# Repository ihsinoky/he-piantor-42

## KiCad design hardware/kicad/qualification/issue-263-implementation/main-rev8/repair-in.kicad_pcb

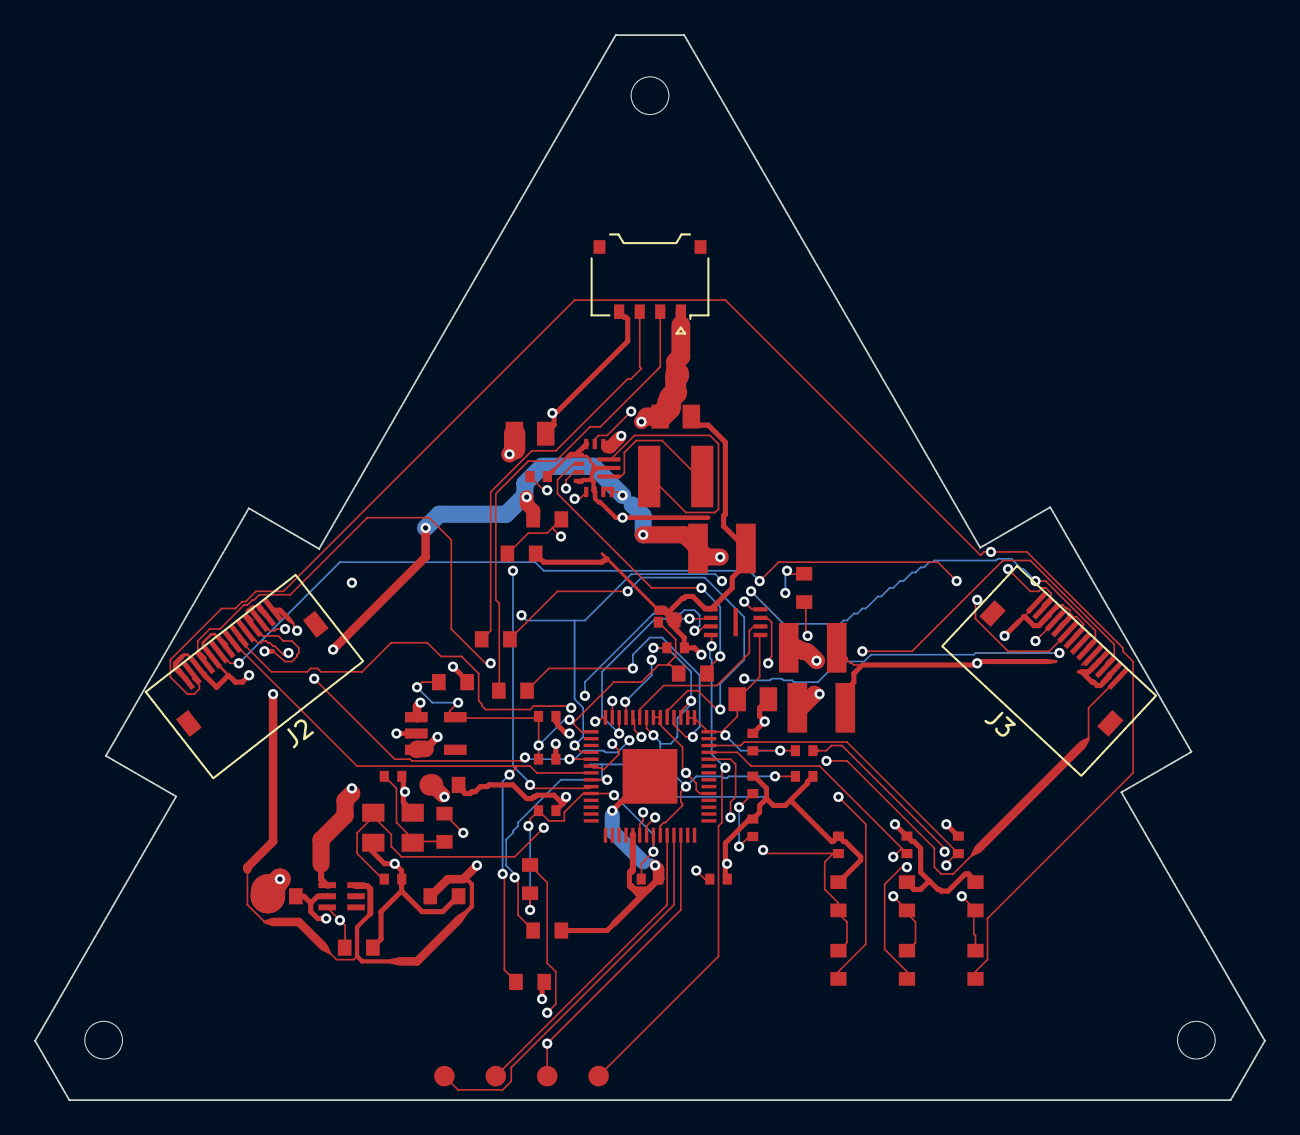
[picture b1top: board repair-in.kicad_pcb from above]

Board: 4 copper layers, 71.8 x 62.2 mm, 62 parts (0 on the bottom side), 40 nets.

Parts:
C1: 15pF; C1
C2: 15pF; C2
C3: 100nF; C3
C4: 100nF; C4
C5: 100nF; C5
C6: 100nF; C6
C7: 100nF; C7
C8: 100nF; C8
C9: 100nF; C9
C10: 100nF; C10
C11: 100nF; C11
C12: 1uF; C12
C13: 1uF; C13
C14: 10uF; C14
C15: 100nF; C15
C16: 1uF; C16
C17: 1uF; C17
C18: 1uF; C18
C19: 1uF; C19
C20: 1nF; C20
C21: 1nF; C21
C22: 1nF; C22
C23: 22uF 16V X6S 0805; C23
C24: 22uF 16V X6S 0805; C24
C25: 100nF; C25
C26: 22uF 16V X7R 1210; C26
C27: 22uF 16V X7R 1210; C27
C28: 22uF 16V X7R 1210; C28
H1: NPTH_2.2mm; H1
H2: NPTH_2.2mm; H2
H3: NPTH_2.2mm; H3
J2, J3: FH12-14S-0.5SH(55); Hirose_FH12-14S-0.5SH_1x14-1MP_P0.50mm_Horizontal
J4: 781710004; J4
L1: 1.5uH XFL4020-152MEC; L1
R3: 27; R3
R4: 27; R4
R5: 1k; R5
R6: 100k; R6
R7: 100k; R7
R8: 10k; R8
R9: 1k; R9
R10: 6.8k; R10
R11: 10k; R11
R12: 6.8k; R12
R13: 10k; R13
R14: 6.8k; R14
R15: 10k; R15
R16: 100k; R16
R17: 54.9k 0.1% 25ppm/K; R17
R18: 10k 0.1% 25ppm/K; R18
R19: 100k; R19
TP1: TestPoint; TP1
TP2: TestPoint; TP2
TP3: TestPoint; TP3
TP4: TestPoint; TP4
U1: RP2040; U1
U3: W25Q16JVUXIQ; U3
U4: AP2112K-3.3TRG1; U4
U5: TPS22919DCKR; U5
U6: TPS63070RNMR; U6
Y1: ABM8-272-T3; Y1

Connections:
ADC_A: C20.1, R10.2, R11.1, U1.38
ADC_B: C21.1, R12.2, R13.1, U1.39
ADC_C: C22.1, R14.2, R15.1, U1.40
FB_5V2: R17.2, R18.1, U6.5
GND: C1.2, C2.2, C3.2, C4.2, C5.2, C6.2, C7.2, C8.2, C9.2, C10.2, C11.2, C12.2, C13.2, C14.2, C15.2, C16.2, C17.2, C18.2, C19.2, C20.2, C21.2, C22.2, C23.2, C24.2, C25.2, C26.2, C27.2, C28.2, J2.1, J2.3, J2.5, J2.7, J2.11, J2.13, J3.1, J3.3, J3.5, J3.7, J3.11, J3.13, J4.4, R6.2, R7.2, R11.2, R13.2, R15.2, R16.2, R18.2, U1.19, U1.57, U3.4, U4.2, U5.2, U6.1, U6.4, U6.6, U6.10, U6.15, Y1.2, Y1.4
HALL_5V: C19.1, J2.14, J3.14, U5.6
HALL_PWR_EN: R7.1, U1.9, U5.3, U6.14
MUX_A0: J2.12, J3.12, U1.4
MUX_A1: J2.10, J3.10, U1.5
MUX_A2: J2.9, J3.9, U1.6
MUX_EN1: J3.8, R16.1, U1.8
MUX_OUT_A: J2.6, J3.6, R10.1
MUX_OUT_B: J2.4, J3.4, R12.1
MUX_OUT_C: J2.2, J3.2, R14.1
QSPI_SCLK: U1.52, U3.6
QSPI_SD0: U1.53, U3.5
QSPI_SD1: U1.55, U3.2
QSPI_SD2: U1.54, U3.3
QSPI_SD3: U1.51, U3.7
QSPI_SS_FLASH: R5.2, TP4.1, U3.1
QSPI_SS_MCU: R5.1, U1.56
RAIL_PG: R19.2, U6.2
RUN: R8.2, TP3.1, U1.26
SW1: L1.1, U6.11
SW2: L1.2, U6.9
SWCLK: TP2.1, U1.24
SWDIO: TP1.1, U1.25
USB_DM: R4.2, U1.46
USB_DM_ESD: J4.2, R4.1
USB_DP: R3.2, U1.47
USB_DP_ESD: J4.3, R3.1
V1V1: C11.1, C13.1, U1.23, U1.45, U1.50
V3V3: C3.1, C4.1, C5.1, C6.1, C7.1, C8.1, C9.1, C10.1, C12.1, C14.1, C15.1, C17.1, R8.1, R19.1, U1.1, U1.10, U1.22, U1.33, U1.42, U1.43, U1.44, U1.48, U1.49, U3.8, U4.5
V5V2: C26.1, C27.1, C28.1, R17.1, U5.1, U6.7, U6.8
VAUX: C25.1, U6.3
VBUS: C16.1, C18.1, C23.1, C24.1, J4.1, U4.1, U4.3, U6.12, U6.13
WING_EN: J2.8, R6.1, U1.7
XIN: C1.1, U1.20, Y1.1
XOUT: R9.2, U1.21
XOUT_XTAL: C2.1, R9.1, Y1.3

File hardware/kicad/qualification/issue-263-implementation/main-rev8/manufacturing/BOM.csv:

Comment,Designator,Footprint,LCSC Part #,Quantity
1.5uH XFL4020-152MEC,L1,L1,,1
100k,R16,R16,,1
100k,R19,R19,,1
100k,R6,R6,,1
100k,R7,R7,,1
100nF,C10,C10,,1
100nF,C11,C11,,1
100nF,C15,C15,,1
100nF,C25,C25,,1
100nF,C3,C3,,1
100nF,C4,C4,,1
100nF,C5,C5,,1
100nF,C6,C6,,1
100nF,C7,C7,,1
100nF,C8,C8,,1
100nF,C9,C9,,1
10k,R11,R11,,1
10k,R13,R13,,1
10k,R15,R15,,1
10k,R8,R8,,1
10k 0.1% 25ppm/K,R18,R18,,1
10uF,C14,C14,,1
15pF,C1,C1,,1
15pF,C2,C2,,1
1k,R5,R5,,1
1k,R9,R9,,1
1nF,C20,C20,,1
1nF,C21,C21,,1
1nF,C22,C22,,1
1uF,C12,C12,,1
1uF,C13,C13,,1
1uF,C16,C16,,1
1uF,C17,C17,,1
1uF,C18,C18,,1
1uF,C19,C19,,1
22uF 16V X6S 0805,C23,C23,,1
22uF 16V X6S 0805,C24,C24,,1
22uF 16V X7R 1210,C26,C26,,1
22uF 16V X7R 1210,C27,C27,,1
22uF 16V X7R 1210,C28,C28,,1
27,R3,R3,,1
27,R4,R4,,1
54.9k 0.1% 25ppm/K,R17,R17,,1
6.8k,R10,R10,,1
6.8k,R12,R12,,1
6.8k,R14,R14,,1
781710004,J4,J4,,1
ABM8-272-T3,Y1,Y1,,1
AP2112K-3.3TRG1,U4,U4,,1
FH12-14S-0.5SH(55),"J2,J3",Hirose_FH12-14S-0.5SH_1x14-1MP_P0.50mm_Horizontal,C-HIROSE-FH12-14S,2
NPTH_2.2mm,H1,H1,,1
NPTH_2.2mm,H2,H2,,1
NPTH_2.2mm,H3,H3,,1
RP2040,U1,U1,,1
TPS22919DCKR,U5,U5,,1
TPS63070RNMR,U6,U6,,1
TestPoint,TP1,TP1,,1
TestPoint,TP2,TP2,,1
TestPoint,TP3,TP3,,1
TestPoint,TP4,TP4,,1
W25Q16JVUXIQ,U3,U3,,1

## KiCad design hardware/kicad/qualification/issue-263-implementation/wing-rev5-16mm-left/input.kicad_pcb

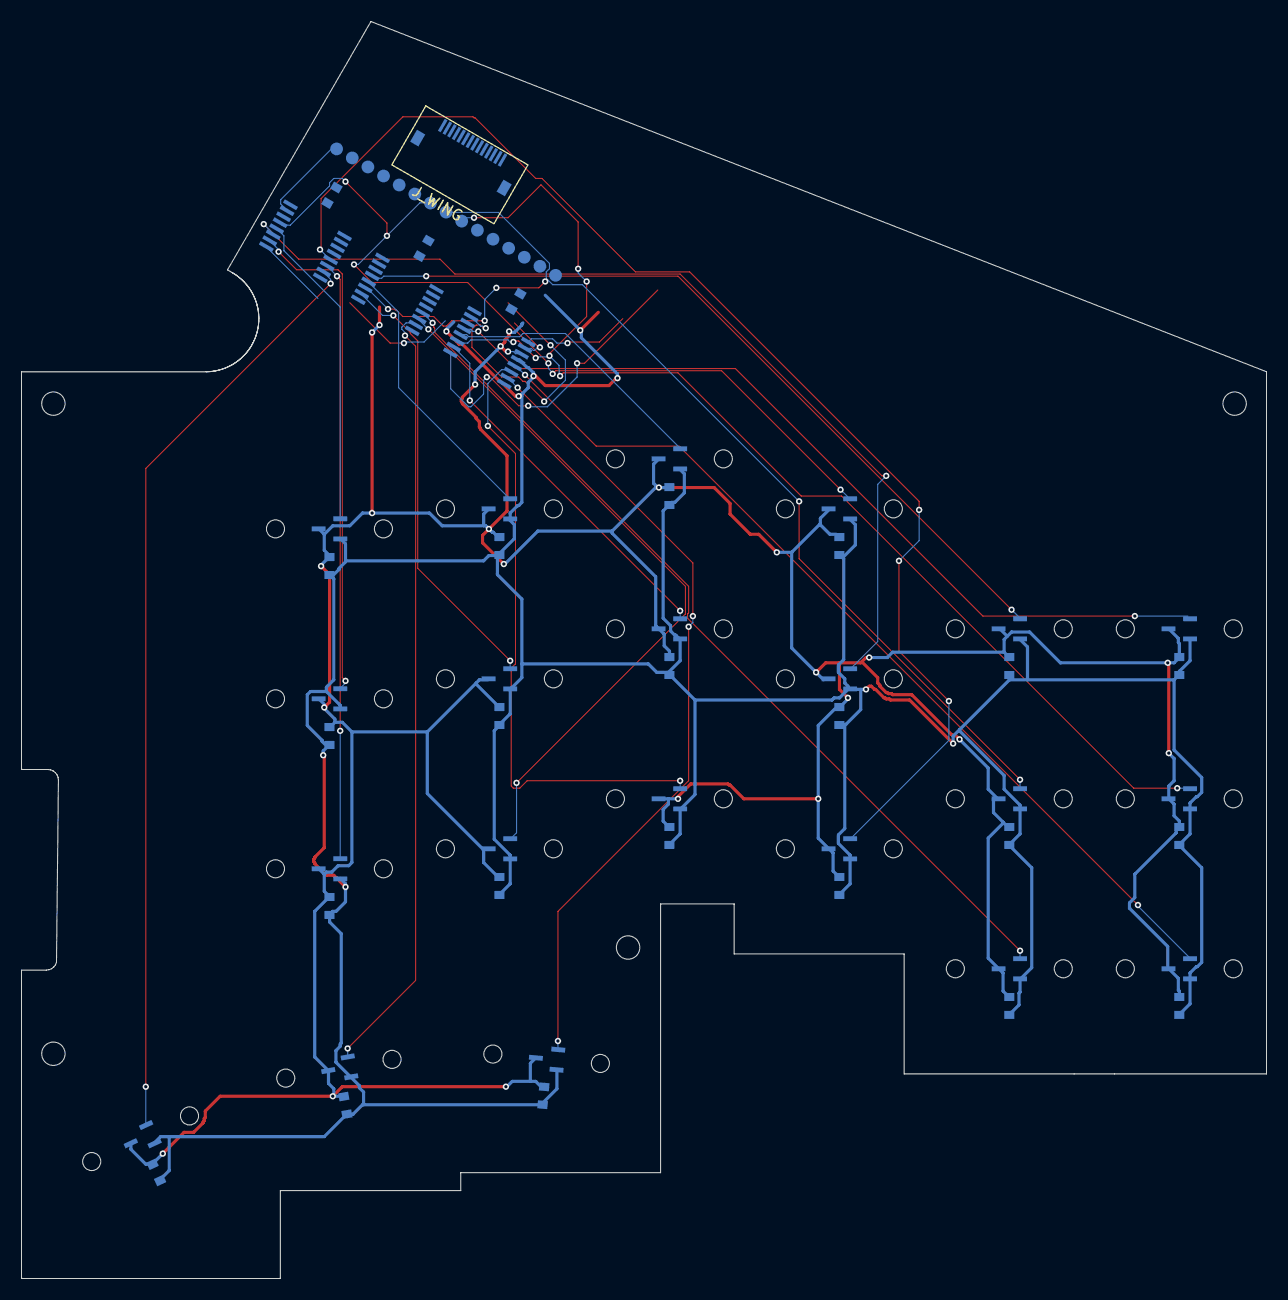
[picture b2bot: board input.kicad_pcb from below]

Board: 2 copper layers, 117.2 x 118.3 mm, 110 parts (64 on the bottom side), 30 nets.

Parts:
C_HA0, C_HA1, C_HA2, C_HA3, C_HA4, C_HA5, C_HA6: GRM188R71C104KA01D; capacitor
C_HB0, C_HB1, C_HB2, C_HB3, C_HB4, C_HB5, C_HB6: GRM188R71C104KA01D; capacitor
C_HC0, C_HC1, C_HC2, C_HC3, C_HC4, C_HC5, C_HC6: GRM188R71C104KA01D; capacitor
C_MUX_A: GRM188R71C104KA01D; capacitor
C_MUX_B: GRM188R71C104KA01D; capacitor
C_MUX_C: GRM188R71C104KA01D; capacitor
H1, H2, H3, H4: NPTH_2.2; NPTH
J_WING: FH12-14S-0.5SH(55); Hirose_FH12-14S-0.5SH_1x14-1MP_P0.50mm_Horizontal
MH_1_1, MH_1_2, MH_2_1, MH_2_2, MH_3_1, MH_3_2, MH_4_1, MH_4_2, MH_5_1, MH_5_2, MH_6_1, MH_6_2, MH_7_1, MH_7_2, MH_8_1, MH_8_2, MH_9_1, MH_9_2, MH_10_1, MH_10_2, MH_11_1, MH_11_2, MH_12_1, MH_12_2, MH_13_1, MH_13_2, MH_14_1, MH_14_2, MH_15_1, MH_15_2, MH_16_1, MH_16_2, MH_17_1, MH_17_2, MH_18_1, MH_18_2, MH_19_1, MH_19_2, MH_20_1, MH_20_2, MH_21_1, MH_21_2: NPTH_1.7; NPTH
TP_H_CTR_RAW: PCB_PAD_1.2MM; testpoint
TP_H_DIAG_RAW: PCB_PAD_1.2MM; testpoint
TP_H_N_RAW: PCB_PAD_1.2MM; testpoint
TP_W_A0, TP_W_A1, TP_W_A2: PCB_PAD_1.2MM; testpoint
TP_W_EN: PCB_PAD_1.2MM; testpoint
TP_W_GND: PCB_PAD_1.2MM; testpoint
TP_W_GND_A: PCB_PAD_1.2MM; testpoint
TP_W_GND_B: PCB_PAD_1.2MM; testpoint
TP_W_GND_C: PCB_PAD_1.2MM; testpoint
TP_W_H5V: PCB_PAD_1.2MM; testpoint
TP_W_MUXA: PCB_PAD_1.2MM; testpoint
TP_W_MUXB: PCB_PAD_1.2MM; testpoint
TP_W_MUXC: PCB_PAD_1.2MM; testpoint
U_HA0, U_HA1, U_HA2, U_HA3, U_HA4, U_HA5, U_HA6: DRV5055A3QDBZR; hall
U_HB0, U_HB1, U_HB2, U_HB3, U_HB4, U_HB5, U_HB6: DRV5055A3QDBZR; hall
U_HC0, U_HC1, U_HC2, U_HC3, U_HC4, U_HC5, U_HC6: DRV5055A3QDBZR; hall
U_MUX_A: TMUX1208PWR; mux
U_MUX_B: TMUX1208PWR; mux
U_MUX_C: TMUX1208PWR; mux

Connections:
GND: C_HA0.2, C_HA1.2, C_HA2.2, C_HA3.2, C_HA4.2, C_HA5.2, C_HA6.2, C_HB0.2, C_HB1.2, C_HB2.2, C_HB3.2, C_HB4.2, C_HB5.2, C_HB6.2, C_HC0.2, C_HC1.2, C_HC2.2, C_HC3.2, C_HC4.2, C_HC5.2, C_HC6.2, C_MUX_A.2, C_MUX_B.2, C_MUX_C.2, J_WING.2, J_WING.4, J_WING.8, J_WING.10, J_WING.12, J_WING.14, TP_W_GND.1, TP_W_GND_A.1, TP_W_GND_B.1, TP_W_GND_C.1, U_HA0.3, U_HA1.3, U_HA2.3, U_HA3.3, U_HA4.3, U_HA5.3, U_HA6.3, U_HB0.3, U_HB1.3, U_HB2.3, U_HB3.3, U_HB4.3, U_HB5.3, U_HB6.3, U_HC0.3, U_HC1.3, U_HC2.3, U_HC3.3, U_HC4.3, U_HC5.3, U_HC6.3, U_MUX_A.14, U_MUX_B.14, U_MUX_C.14
HALL_5V: C_HA0.1, C_HA1.1, C_HA2.1, C_HA3.1, C_HA4.1, C_HA5.1, C_HA6.1, C_HB0.1, C_HB1.1, C_HB2.1, C_HB3.1, C_HB4.1, C_HB5.1, C_HB6.1, C_HC0.1, C_HC1.1, C_HC2.1, C_HC3.1, C_HC4.1, C_HC5.1, C_HC6.1, C_MUX_A.1, C_MUX_B.1, C_MUX_C.1, J_WING.1, TP_W_H5V.1, U_HA0.1, U_HA1.1, U_HA2.1, U_HA3.1, U_HA4.1, U_HA5.1, U_HA6.1, U_HB0.1, U_HB1.1, U_HB2.1, U_HB3.1, U_HB4.1, U_HB5.1, U_HB6.1, U_HC0.1, U_HC1.1, U_HC2.1, U_HC3.1, U_HC4.1, U_HC5.1, U_HC6.1, U_MUX_A.13, U_MUX_B.13, U_MUX_C.13
H_A0_RAW: U_HA0.2, U_MUX_A.4
H_A1_RAW: U_HA1.2, U_MUX_A.5
H_A2_RAW: TP_H_CTR_RAW.1, U_HA2.2, U_MUX_A.6
H_A3_RAW: U_HA3.2, U_MUX_A.7
H_A4_RAW: U_HA4.2, U_MUX_A.12
H_A5_RAW: U_HA5.2, U_MUX_A.11
H_A6_RAW: U_HA6.2, U_MUX_A.10
H_B0_RAW: U_HB0.2, U_MUX_B.4
H_B1_RAW: U_HB1.2, U_MUX_B.5
H_B2_RAW: TP_H_N_RAW.1, U_HB2.2, U_MUX_B.6
H_B3_RAW: U_HB3.2, U_MUX_B.7
H_B4_RAW: U_HB4.2, U_MUX_B.12
H_B5_RAW: U_HB5.2, U_MUX_B.11
H_B6_RAW: U_HB6.2, U_MUX_B.10
H_C0_RAW: TP_H_DIAG_RAW.1, U_HC0.2, U_MUX_C.4
H_C1_RAW: U_HC1.2, U_MUX_C.5
H_C2_RAW: U_HC2.2, U_MUX_C.6
H_C3_RAW: U_HC3.2, U_MUX_C.7
H_C4_RAW: U_HC4.2, U_MUX_C.12
H_C5_RAW: U_HC5.2, U_MUX_C.11
H_C6_RAW: U_HC6.2, U_MUX_C.10
MUX_A0: J_WING.3, TP_W_A0.1, U_MUX_A.1, U_MUX_B.1, U_MUX_C.1
MUX_A1: J_WING.5, TP_W_A1.1, U_MUX_A.16, U_MUX_B.16, U_MUX_C.16
MUX_A2: J_WING.6, TP_W_A2.1, U_MUX_A.15, U_MUX_B.15, U_MUX_C.15
MUX_OUT_A: J_WING.9, TP_W_MUXA.1, U_MUX_A.8
MUX_OUT_B: J_WING.11, TP_W_MUXB.1, U_MUX_B.8
MUX_OUT_C: J_WING.13, TP_W_MUXC.1, U_MUX_C.8
WING_EN: J_WING.7, TP_W_EN.1, U_MUX_A.2, U_MUX_B.2, U_MUX_C.2

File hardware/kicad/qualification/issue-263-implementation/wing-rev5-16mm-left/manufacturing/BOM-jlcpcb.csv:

Comment,Designator,Footprint,LCSC Part #
DRV5055A3QDBZR,"U_HA0,U_HA1,U_HA2,U_HA3,U_HA4,U_HA5,U_HA6,U_HB0,U_HB1,U_HB2,U_HB3,U_HB4,U_HB5,U_HB6,U_HC0,U_HC1,U_HC2,U_HC3,U_HC4,U_HC5,U_HC6",hall,C266128
FH12-14S-0.5SH(55),J_WING,Hirose_FH12-14S-0.5SH_1x14-1MP_P0.50mm_Horizontal,C-HIROSE-FH12-14S
GRM188R71C104KA01D,"C_HA0,C_HA1,C_HA2,C_HA3,C_HA4,C_HA5,C_HA6,C_HB0,C_HB1,C_HB2,C_HB3,C_HB4,C_HB5,C_HB6,C_HC0,C_HC1,C_HC2,C_HC3,C_HC4,C_HC5,C_HC6,C_MUX_A,C_MUX_B,C_MUX_C",capacitor,C45000
TMUX1208PWR,"U_MUX_A,U_MUX_B,U_MUX_C",mux,C494728
